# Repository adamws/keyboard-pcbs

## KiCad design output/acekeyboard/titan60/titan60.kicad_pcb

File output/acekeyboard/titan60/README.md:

## acekeyboard/titan60

[layout](titan60-kle.json) - [PCB](titan60.kicad_pcb)

{:loading="lazy"}

[Open in keyboard-layout-editor](http://www.keyboard-layout-editor.com/##@@_y:1;&=0,0&=0,1&=0,2&=0,3&=0,4&=0,5&=0,6&=0,7&=0,8&=0,9&=0,10&=0,11&=0,12&_c=#aaaaaa&w:2;&=0,13%0A%0A%0A0,0;&@_w:1.5;&=1,0&_c=#cccccc;&=1,1&=1,2&=1,3&=1,4&=1,5&=1,6&=1,7&=1,8&=1,9&=1,10&=1,11&=1,12&_c=#aaaaaa&w:1.5;&=1,13%0A%0A%0A1,0;&@_w:1.75;&=2,0&_c=#cccccc;&=2,1&=2,2&=2,3&=2,4&=2,5&=2,6&=2,7&=2,8&=2,9&=2,10&=2,11&_c=#aaaaaa&w:2.25;&=2,13%0A%0A%0A1,0;&@_w:2.25;&=3,0%0A%0A%0A2,0&_c=#cccccc;&=3,2%0A%0A%0A2,0&=3,3%0A%0A%0A2,0&=3,4%0A%0A%0A2,0&=3,5%0A%0A%0A2,0&=3,6%0A%0A%0A2,0&=3,7%0A%0A%0A2,0&=3,8%0A%0A%0A2,0&=3,9%0A%0A%0A2,0&=3,10%0A%0A%0A2,0&=3,11%0A%0A%0A2,0&_c=#aaaaaa&w:2.75;&=3,12%0A%0A%0A2,0;&@_w:1.25;&=4,0%0A%0A%0A3,0&_w:1.25;&=4,1%0A%0A%0A3,0&_w:1.25;&=4,2%0A%0A%0A3,0&_c=#cccccc&w:6.25;&=4,6%0A%0A%0A3,0&_c=#aaaaaa&w:1.25;&=4,10%0A%0A%0A3,0&_w:1.25;&=4,11%0A%0A%0A3,0&_w:1.25;&=4,12%0A%0A%0A3,0&_w:1.25;&=4,13%0A%0A%0A3,0;&@_x:13&y:-6;&=0,13%0A%0A%0A0,1&=2,12%0A%0A%0A0,1;&@_x:16.5&y:1&w:1.25&h:2&w2:1.5&h2:1&x2:-0.25;&=2,13%0A%0A%0A1,1;&@_x:15.5&c=#cccccc;&=1,13%0A%0A%0A1,1;&@_y:2.5&c=#aaaaaa&w:2;&=3,0%0A%0A%0A2,1&_c=#cccccc;&=3,2%0A%0A%0A2,1&=3,3%0A%0A%0A2,1&=3,4%0A%0A%0A2,1&=3,5%0A%0A%0A2,1&=3,6%0A%0A%0A2,1&=3,7%0A%0A%0A2,1&=3,8%0A%0A%0A2,1&=3,9%0A%0A%0A2,1&=3,10%0A%0A%0A2,1&=3,11%0A%0A%0A2,1&_c=#aaaaaa;&=3,13%0A%0A%0A2,1&=3,12%0A%0A%0A2,1&=4,3%0A%0A%0A2,1;&@_w:2.25;&=3,0%0A%0A%0A2,2&_c=#cccccc;&=3,2%0A%0A%0A2,2&=3,3%0A%0A%0A2,2&=3,4%0A%0A%0A2,2&=3,5%0A%0A%0A2,2&=3,6%0A%0A%0A2,2&=3,7%0A%0A%0A2,2&=3,8%0A%0A%0A2,2&=3,9%0A%0A%0A2,2&=3,10%0A%0A%0A2,2&=3,11%0A%0A%0A2,2&_c=#aaaaaa&w:1.75;&=3,12%0A%0A%0A2,2&=4,3%0A%0A%0A2,2;&@_w:1.25;&=3,0%0A%0A%0A2,3&_c=#cccccc;&=3,1%0A%0A%0A2,3&=3,2%0A%0A%0A2,3&=3,3%0A%0A%0A2,3&=3,4%0A%0A%0A2,3&=3,5%0A%0A%0A2,3&=3,6%0A%0A%0A2,3&=3,7%0A%0A%0A2,3&=3,8%0A%0A%0A2,3&=3,9%0A%0A%0A2,3&=3,10%0A%0A%0A2,3&=3,11%0A%0A%0A2,3&_c=#aaaaaa&w:2.75;&=3,12%0A%0A%0A2,3;&@_w:1.25;&=3,0%0A%0A%0A2,4&_c=#cccccc;&=3,1%0A%0A%0A2,4&=3,2%0A%0A%0A2,4&=3,3%0A%0A%0A2,4&=3,4%0A%0A%0A2,4&=3,5%0A%0A%0A2,4&=3,6%0A%0A%0A2,4&=3,7%0A%0A%0A2,4&=3,8%0A%0A%0A2,4&=3,9%0A%0A%0A2,4&=3,10%0A%0A%0A2,4&=3,11%0A%0A%0A2,4&_c=#aaaaaa&w:1.75;&=3,12%0A%0A%0A2,4&=4,3%0A%0A%0A2,4;&@_y:0.5&w:1.5;&=4,0%0A%0A%0A3,1&=4,1%0A%0A%0A3,1&_w:1.5;&=4,2%0A%0A%0A3,1&_c=#cccccc&w:7;&=4,6%0A%0A%0A3,1&_c=#aaaaaa&w:1.5;&=4,11%0A%0A%0A3,1&=4,12%0A%0A%0A3,1&_w:1.5;&=4,13%0A%0A%0A3,1;&@_w:1.25;&=4,0%0A%0A%0A3,2&_w:1.25;&=4,1%0A%0A%0A3,2&_w:1.25;&=4,2%0A%0A%0A3,2&_c=#cccccc&w:2.75;&=4,4%0A%0A%0A3,2&_w:1.25;&=4,6%0A%0A%0A3,2&_w:2.25;&=4,8%0A%0A%0A3,2&_c=#aaaaaa;&=4,10%0A%0A%0A3,2&=4,11%0A%0A%0A3,2&=4,9%0A%0A%0A3,2&=4,12%0A%0A%0A3,2&=4,13%0A%0A%0A3,2)

{:loading="lazy"}

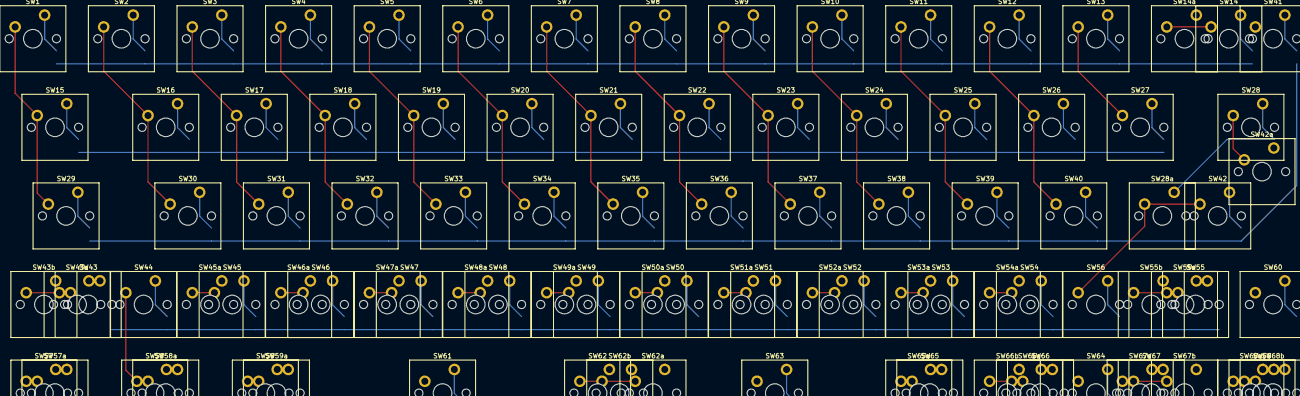
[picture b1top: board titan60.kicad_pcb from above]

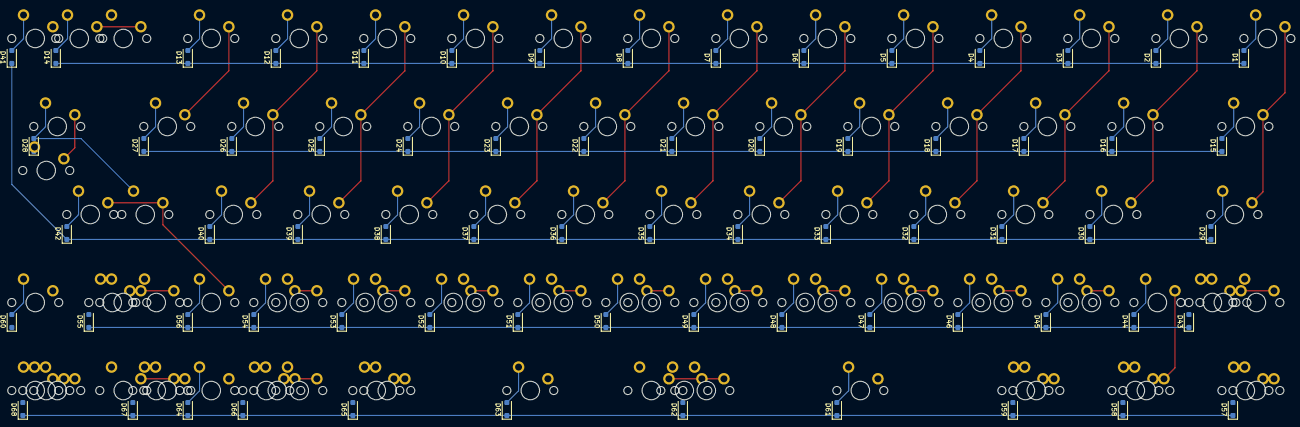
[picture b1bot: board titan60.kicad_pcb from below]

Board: 2 copper layers, 165 parts (68 on the bottom side), 87 nets.

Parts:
D1, D2, D3, D4, D5, D6, D7, D8, D9, D10, D11, D12, D13, D14, D15, D16, D17, D18, D19, D20, D21, D22, D23, D24, D25, D26, D27, D28, D29, D30, D31, D32, D33, D34, D35, D36, D37, D38, D39, D40, D41, D42, D43, D44, D45, D46, D47, D48, D49, D50, D51, D52, D53, D54, D55, D56, D57, D58, D59, D60, D61, D62, D63, D64, D65, D66, D67, D68: D_SOD-123F
SW1, SW2, SW3, SW4, SW5, SW6, SW7, SW8, SW9, SW10, SW11, SW12, SW13, SW14, SW14a, SW15, SW16, SW17, SW18, SW19, SW20, SW21, SW22, SW23, SW24, SW25, SW26, SW27, SW28, SW28a, SW29, SW30, SW31, SW32, SW33, SW34, SW35, SW36, SW37, SW38, SW39, SW40, SW41, SW42, SW42a, SW43, SW43a, SW43b, SW44, SW45, SW45a, SW46, SW46a, SW47, SW47a, SW48, SW48a, SW49, SW49a, SW50, SW50a, SW51, SW51a, SW52, SW52a, SW53, SW53a, SW54, SW54a, SW55, SW55a, SW55b, SW56, SW57, SW57a, SW58, SW58a, SW59, SW59a, SW60, SW61, SW62, SW62a, SW62b, SW63, SW64, SW65, SW65a, SW66, SW66a, SW66b, SW67, SW67a, SW67b, SW68, SW68a, SW68b: SW_Cherry_MX_PCB_1.00u

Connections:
COL0: SW1.1, SW15.1, SW29.1, SW43.1, SW43a.1, SW43b.1, SW57.1, SW57a.1
COL1: SW2.1, SW16.1, SW30.1, SW44.1, SW58.1, SW58a.1
COL2: SW3.1, SW17.1, SW31.1, SW45.1, SW45a.1, SW59.1, SW59a.1
COL3: SW4.1, SW18.1, SW32.1, SW46.1, SW46a.1, SW60.1
COL4: SW5.1, SW19.1, SW33.1, SW47.1, SW47a.1, SW61.1
COL5: SW6.1, SW20.1, SW34.1, SW48.1, SW48a.1
COL6: SW7.1, SW21.1, SW35.1, SW49.1, SW49a.1, SW62.1, SW62a.1, SW62b.1
COL7: SW8.1, SW22.1, SW36.1, SW50.1, SW50a.1
COL8: SW9.1, SW23.1, SW37.1, SW51.1, SW51a.1, SW63.1
COL9: SW10.1, SW24.1, SW38.1, SW52.1, SW52a.1, SW64.1
COL10: SW11.1, SW25.1, SW39.1, SW53.1, SW53a.1, SW65.1, SW65a.1
COL11: SW12.1, SW26.1, SW40.1, SW54.1, SW54a.1, SW66.1, SW66a.1, SW66b.1
COL12: SW13.1, SW27.1, SW41.1, SW55.1, SW55a.1, SW55b.1, SW67.1, SW67a.1, SW67b.1
COL13: SW14.1, SW14a.1, SW28.1, SW28a.1, SW42.1, SW42a.1, SW56.1, SW68.1, SW68a.1, SW68b.1
unnamed: D1.2, SW1.2
unnamed: D2.2, SW2.2
unnamed: D3.2, SW3.2
unnamed: D4.2, SW4.2
unnamed: D5.2, SW5.2
unnamed: D6.2, SW6.2
unnamed: D7.2, SW7.2
unnamed: D8.2, SW8.2
unnamed: D9.2, SW9.2
unnamed: D10.2, SW10.2
unnamed: D11.2, SW11.2
unnamed: D12.2, SW12.2
unnamed: D13.2, SW13.2
unnamed: D14.2, SW14.2, SW14a.2
unnamed: D15.2, SW15.2
unnamed: D16.2, SW16.2
unnamed: D17.2, SW17.2
unnamed: D18.2, SW18.2
unnamed: D19.2, SW19.2
unnamed: D20.2, SW20.2
unnamed: D21.2, SW21.2
unnamed: D22.2, SW22.2
unnamed: D23.2, SW23.2
unnamed: D24.2, SW24.2
unnamed: D25.2, SW25.2
unnamed: D26.2, SW26.2
unnamed: D27.2, SW27.2
unnamed: D28.2, SW28.2, SW28a.2
unnamed: D29.2, SW29.2
unnamed: D30.2, SW30.2
unnamed: D31.2, SW31.2
unnamed: D32.2, SW32.2
unnamed: D33.2, SW33.2
unnamed: D34.2, SW34.2
unnamed: D35.2, SW35.2
unnamed: D36.2, SW36.2
unnamed: D37.2, SW37.2
unnamed: D38.2, SW38.2
unnamed: D39.2, SW39.2
unnamed: D40.2, SW40.2
unnamed: D41.2, SW41.2
unnamed: D42.2, SW42.2, SW42a.2
unnamed: D43.2, SW43.2, SW43a.2, SW43b.2
unnamed: D44.2, SW44.2
unnamed: D45.2, SW45.2, SW45a.2
unnamed: D46.2, SW46.2, SW46a.2
unnamed: D47.2, SW47.2, SW47a.2
unnamed: D48.2, SW48.2, SW48a.2
unnamed: D49.2, SW49.2, SW49a.2
unnamed: D50.2, SW50.2, SW50a.2
unnamed: D51.2, SW51.2, SW51a.2
unnamed: D52.2, SW52.2, SW52a.2
unnamed: D53.2, SW53.2, SW53a.2
unnamed: D54.2, SW54.2, SW54a.2
unnamed: D55.2, SW55.2, SW55a.2, SW55b.2
unnamed: D56.2, SW56.2
unnamed: D57.2, SW57.2, SW57a.2
unnamed: D58.2, SW58.2, SW58a.2
unnamed: D59.2, SW59.2, SW59a.2
unnamed: D60.2, SW60.2
unnamed: D61.2, SW61.2
unnamed: D62.2, SW62.2, SW62a.2, SW62b.2
unnamed: D63.2, SW63.2
unnamed: D64.2, SW64.2
unnamed: D65.2, SW65.2, SW65a.2
unnamed: D66.2, SW66.2, SW66a.2, SW66b.2
unnamed: D67.2, SW67.2, SW67a.2, SW67b.2
unnamed: D68.2, SW68.2, SW68a.2, SW68b.2
ROW0: D1.1, D2.1, D3.1, D4.1, D5.1, D6.1, D7.1, D8.1, D9.1, D10.1, D11.1, D12.1, D13.1, D14.1
ROW1: D15.1, D16.1, D17.1, D18.1, D19.1, D20.1, D21.1, D22.1, D23.1, D24.1, D25.1, D26.1, D27.1, D28.1
ROW2: D29.1, D30.1, D31.1, D32.1, D33.1, D34.1, D35.1, D36.1, D37.1, D38.1, D39.1, D40.1, D41.1, D42.1
ROW3: D43.1, D44.1, D45.1, D46.1, D47.1, D48.1, D49.1, D50.1, D51.1, D52.1, D53.1, D54.1, D55.1, D56.1
ROW4: D57.1, D58.1, D59.1, D60.1, D61.1, D62.1, D63.1, D64.1, D65.1, D66.1, D67.1, D68.1
